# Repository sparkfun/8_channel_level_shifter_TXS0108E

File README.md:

SparkFun Level Shifter - 8 Channel (TXS01018E) 
===========================================

[*SparkFun Level Shifter - 8 Channel (TXS01018E) (BOB-19626)*](https://www.sparkfun.com/products/19626)

The SparkFun Level Shifter - 8 Channel (TXS01018E) features the TXS01018E<sup>&trade;</sup> 8-bit, bi-directional logic level translator from Texas Instruments to shift between devices running at different common microcontroller voltages such as 1.8V, 3.3V and 5V. The TXS0108E can transmit data between ports at max speeds of 110Mbps (push/pull) or 1.2Mbps (open drain).

Repository Contents
-------------------

* **/Documents** - Datasheet
* **/Hardware** - Eagle design files (.brd, .sch)

Documentation
-------------

* **[Hookup Guide](https://learn.sparkfun.com/tutorials/level-shifter---8-channel-txs0108e-hookup-guide)** - A basic Hookup Guide to get started with the SparkFun Level Shifter - 8 Channel (TXS01018E).

Product Versions
----------------

* **[BOB-19626](https://www.sparkfun.com/products/19626)** - Initial Release

Version History
---------------

* v1.0 - Initial Release

License Information
-------------------

This product is _**open source**_! 

Please review the LICENSE.md file for license information. 

If you have any questions or concerns on licensing, please contact technical support on our [SparkFun forums](https://forum.sparkfun.com/viewforum.php?f=152).

Distributed as-is; no warranty is given.

- Your friends at SparkFun.

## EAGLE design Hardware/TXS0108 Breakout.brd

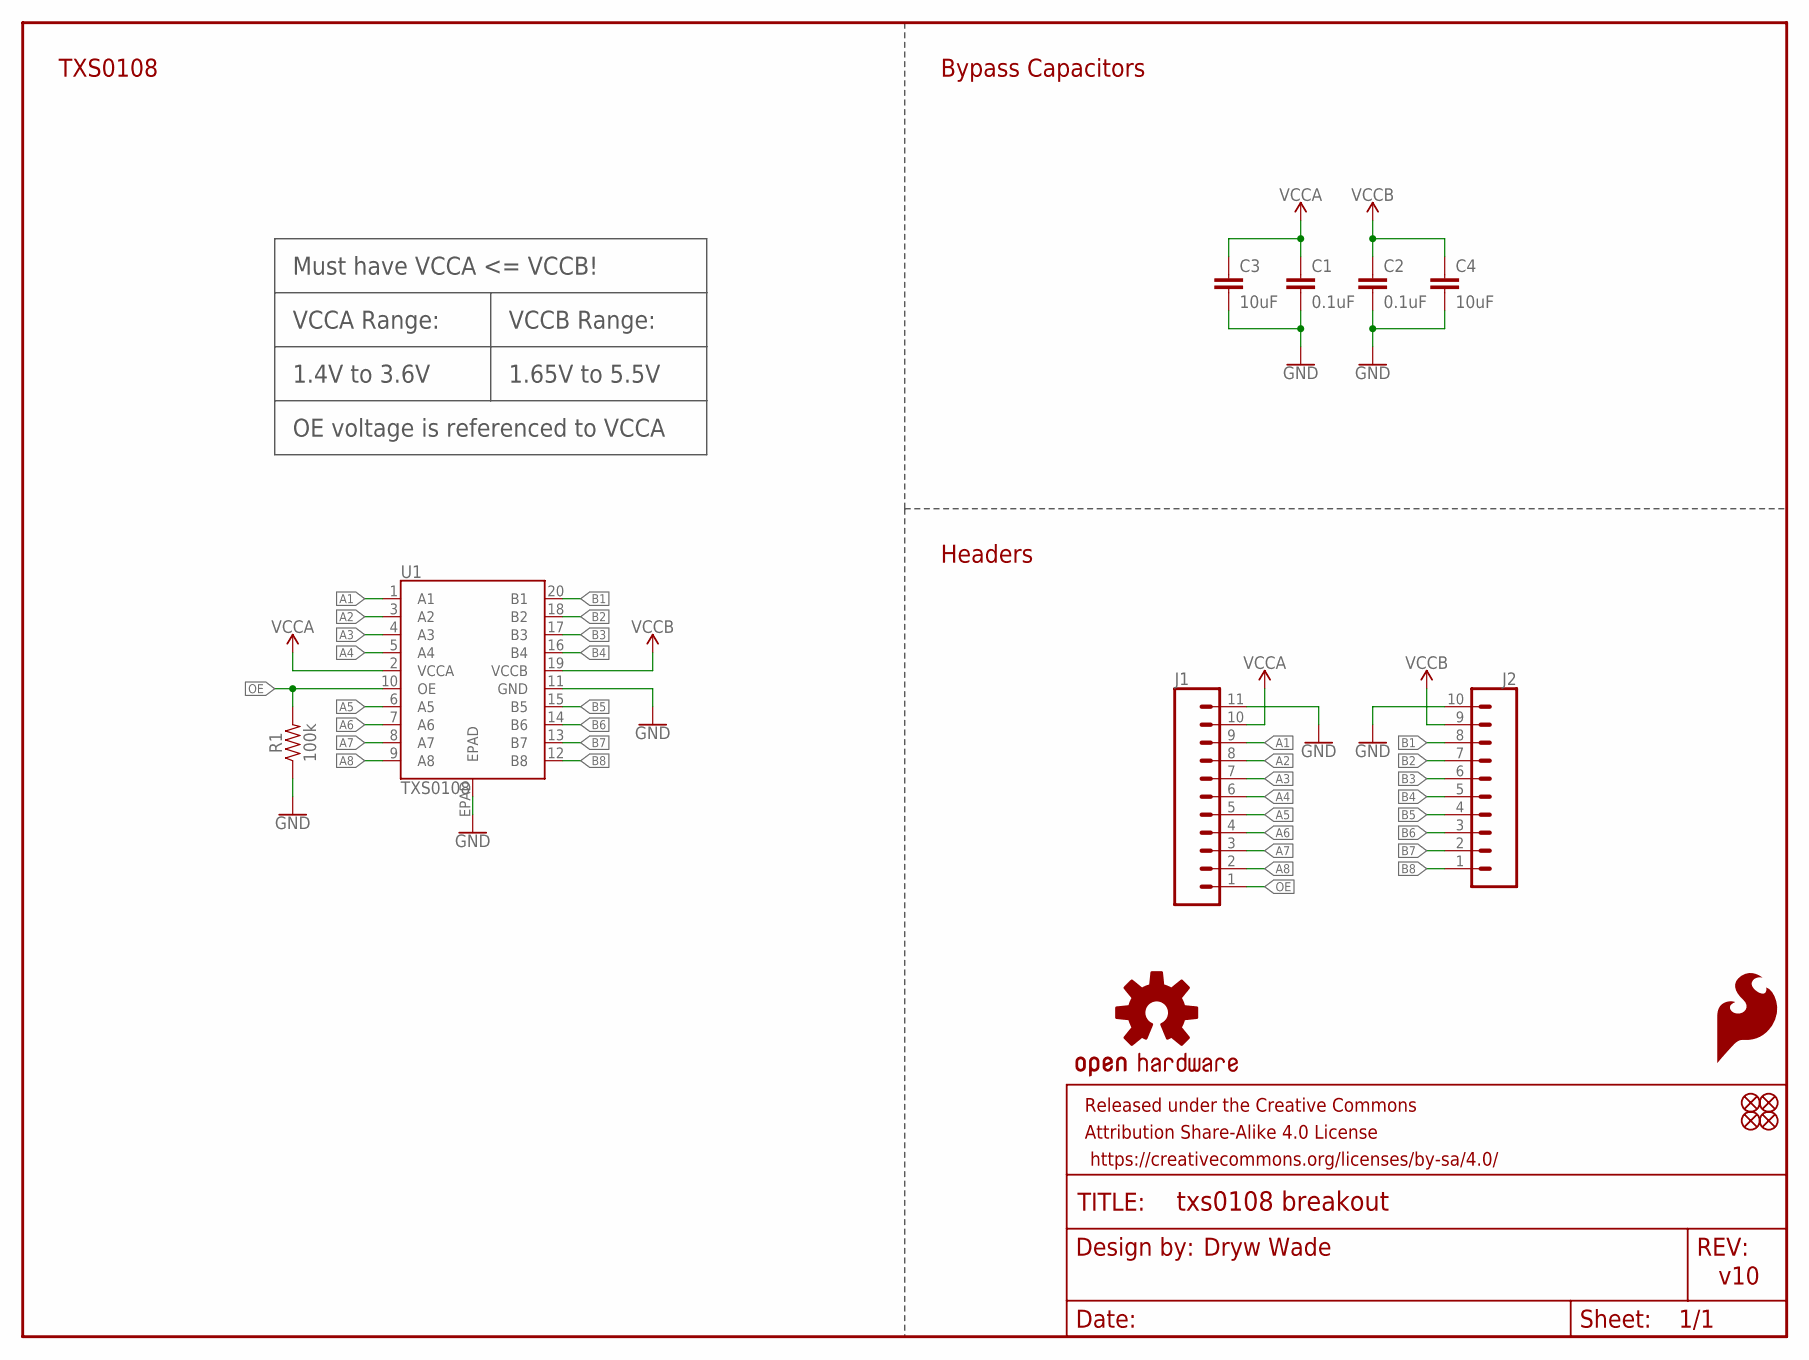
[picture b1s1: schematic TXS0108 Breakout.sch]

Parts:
C1, C2: 0.1uF; 0603
C3, C4: 10uF; 0603
FD1, FD2, FD3, FD4: FIDUCIAL1X2; FIDUCIAL-1X2
FRAME1: FRAME-LETTER; CREATIVE_COMMONS
J1: CONN_111X11_NO_SILK; 1X11_NO_SILK
J2: CONN_10NO_SILK_PTH_FEMALE; 1X10_NO_SILK
LOGO1: OSHW-LOGOS; OSHW-LOGO-S
LOGO2: SFE_LOGO_FLAME.1_INCH; SFE_LOGO_FLAME_.1
R1: 100k; 0603
U1: TXS0108; VFQFN-20

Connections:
A1: J1.9, U1.1 (A1)
A2: J1.8, U1.3 (A2)
A3: J1.7, U1.4 (A3)
A4: J1.6, U1.5 (A4)
A5: J1.5, U1.6 (A5)
A6: J1.4, U1.7 (A6)
A7: J1.3, U1.8 (A7)
A8: J1.2, U1.9 (A8)
B1: J2.8, U1.20 (B1)
B2: J2.7, U1.18 (B2)
B3: J2.6, U1.17 (B3)
B4: J2.5, U1.16 (B4)
B5: J2.4, U1.15 (B5)
B6: J2.3, U1.14 (B6)
B7: J2.2, U1.13 (B7)
B8: J2.1, U1.12 (B8)
GND: C1.2, C2.2, C3.2, C4.2, J1.11, J2.10, R1.1, U1.11 (GND), U1.EPAD
OE: J1.1, R1.2, U1.10 (OE)
VCCA: C1.1, C3.1, J1.10, U1.2 (VCCA)
VCCB: C2.1, C4.1, J2.9, U1.19 (VCCB)

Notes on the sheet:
Must have VCCA <= VCCB!
VCCA Range:
VCCB Range:
1.4V to 3.6V
1.65V to 5.5V
TXS0108
Headers
Bypass Capacitors
OE voltage is referenced to VCCA
Dryw Wade
v10

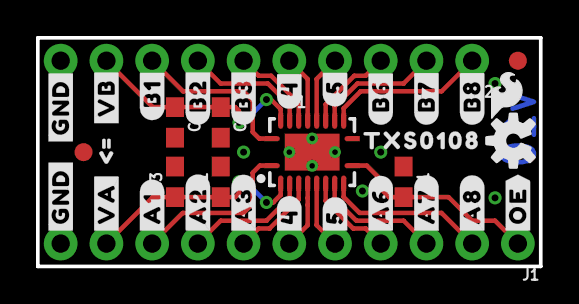
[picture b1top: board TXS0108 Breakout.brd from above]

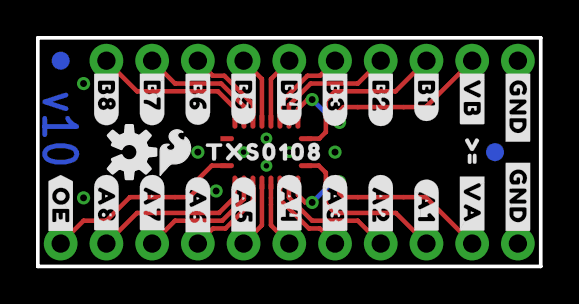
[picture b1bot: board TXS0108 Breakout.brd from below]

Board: 2 copper layers, 27.9 x 12.7 mm, 65 parts (28 on the bottom side), 20 nets.

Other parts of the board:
LOGO3: SFE_LOGO_FLAME.1_INCH; SFE_LOGO_FLAME_.1
LOGO4: OSHW-LOGOS; OSHW-LOGO-S
U$1, U$2, U$32, U$34: #GND#0
U$3, U$4: #VA#0
U$5: #A1#0
U$6: #A2#0
U$7: #A3#0
U$8: #4#0
U$9: #5#0
U$10: #A6#0
U$11: #A7#0
U$12: #A8#0
U$13: #B8#0
U$14: #B7#0
U$15: #B6#0
U$16: #4#6
U$17: #5#6
U$18: #B3#0
U$19: #B2#0
U$20: #B1#0
U$21: #OE#0
U$22, U$23: #VB#0
U$24: #A1#2
U$25: #A2#2
U$26: #A3#3
U$27: #A4#4
U$28: #A5#5
U$29: #A6#6
U$30: #A7#8
U$31: #A8#9
U$33, U$47: #0
U$35: #B8#9
U$36: #B7#9
U$37: #B6#9
U$38: #B5#9
U$39: #B4#9
U$40: #B3#9
U$41: #B2#9
U$42: #B1#9
U$43, U$44: TXS01080
U$45: #OE#1
U$46, U$48: V0

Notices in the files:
parts and their libraries:
SparkFun-Capacitors: Licensing: Creative Commons ShareAlike 4.0 International - https://creativecommons.org/licenses/by-sa/4.0
SparkFun-Aesthetics: Released under the Creative Commons Attribution Share-Alike 4.0 License
SparkFun-Aesthetics: https://creativecommons.org/licenses/by-sa/4.0
